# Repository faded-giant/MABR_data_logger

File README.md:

## Calibrating O2 Sensor

1. Replace ```port="COM8"``` with port number currently assigned to O2 Sensor in ```modbus.py```.
2. Run ``` pip3 install pymodbus```, if necessary in terminal.
3. Run ```python3 modbus.py``` in the directory ```modbus.py``` is located.
4. Script should display ```Raw value: <RAW DEVICE CURRENT> mA, Mapped value: <O2 BASED ON CAL POINTS>%"```
5. Perform a 3 point calibration as follows:
   - For 0% oxygen (```percent_1```), apply pure nitrogen gas to O2 sensor, note raw device current after it is stable.
   - For 10.475% oxygen (```percent_2```), apply a 50% nitrogren gas, 50% Air mixture to O2 sensor, note raw device current after it is stable.
   - For 20.95% oxygen (```percent_3```), apply 100% air to to O2 sensor, note raw device current after it is stable.

6. Replace ```current_1,current_2,current_3``` repectfully with the values noted in previous step.
7. Verify ```Mapped Value``` is as expected for the 3 calibration gases.
8. If all is expected, inside ```config.json```, update the ```current_1,current_2,current_3``` fields in the ```O2_sensor_calibration``` object.

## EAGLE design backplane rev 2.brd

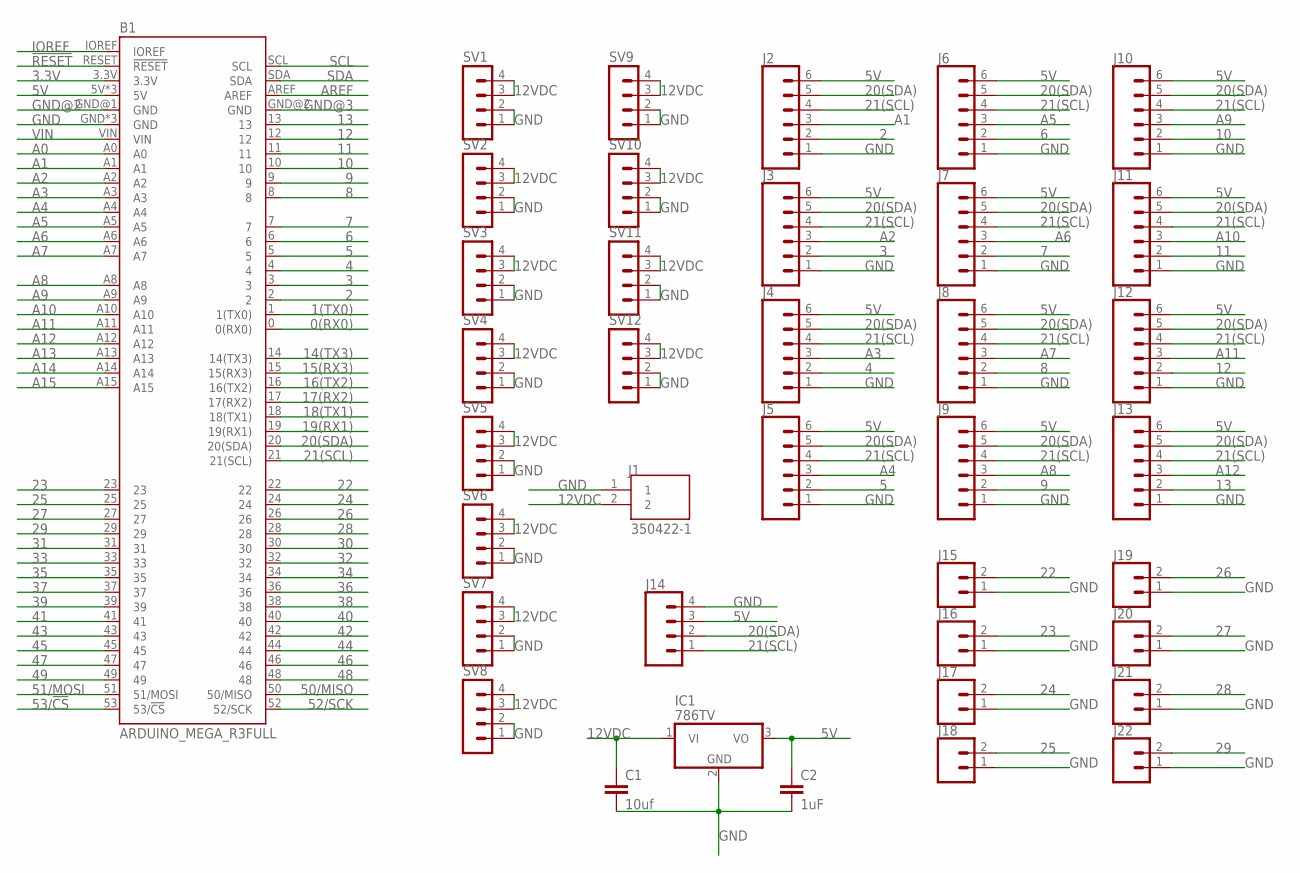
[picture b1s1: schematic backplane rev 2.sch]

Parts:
B1: ARDUINO_MEGA_R3FULL; ARDUINO_MEGA_NO_SILK
C1: 10uf; C2.5-3
C2: 1uF; C2.5-3
IC1: 786TV; TO220V
J1: 350422-1; POWER-PIN
J2, J3, J4, J5, J6, J7, J8, J9, J10, J11, J12, J13: CONN_06NO_SILK_FEMALE_PTH; 1X06_NO_SILK
J14: CONN_04PTH; 1X04
J15, J16, J17, J18, J19, J20, J21, J22: CONN_02; 1X02
SV1, SV2, SV3, SV4, SV5, SV6, SV7, SV8, SV9, SV10, SV11, SV12: MA04-1

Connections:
0(RX0): B1.0 (0(RX0))
1(TX0): B1.1 (1(TX0))
2: B1.2, J2.2
3: B1.3, J3.2
3.3V: B1.3.3V
4: B1.4, J4.2
5: B1.5, J5.2
5V: B1.5V, B1.5V@1 (5V), B1.5V@2 (5V), C2.1, IC1.3 (VO), J2.6, J3.6, J4.6, J5.6, J6.6, J7.6, J8.6, J9.6, J10.6, J11.6, J12.6, J13.6, J14.3
6: B1.6, J6.2
7: B1.7, J7.2
8: B1.8, J8.2
9: B1.9, J9.2
10: B1.10, J10.2
11: B1.11, J11.2
12: B1.12, J12.2
12VDC: C1.1, IC1.1 (VI), J1.2, SV1.3, SV1.4, SV2.3, SV2.4, SV3.3, SV3.4, SV4.3, SV4.4, SV5.3, SV5.4, SV6.3, SV6.4, SV7.3, SV7.4, SV8.3, SV8.4, SV9.3, SV9.4, SV10.3, SV10.4, SV11.3, SV11.4, SV12.3, SV12.4
13: B1.13, J13.2
14(TX3): B1.14 (14(TX3))
15(RX3): B1.15 (15(RX3))
16(TX2): B1.16 (16(TX2))
17(RX2): B1.17 (17(RX2))
18(TX1): B1.18 (18(TX1))
19(RX1): B1.19 (19(RX1))
20(SDA): B1.20 (20(SDA)), J2.5, J3.5, J4.5, J5.5, J6.5, J7.5, J8.5, J9.5, J10.5, J11.5, J12.5, J13.5, J14.2
21(SCL): B1.21 (21(SCL)), J2.4, J3.4, J4.4, J5.4, J6.4, J7.4, J8.4, J9.4, J10.4, J11.4, J12.4, J13.4, J14.1
22: B1.22, J15.2
23: B1.23, J16.2
24: B1.24, J17.2
25: B1.25, J18.2
26: B1.26, J19.2
27: B1.27, J20.2
28: B1.28, J21.2
29: B1.29, J22.2
30: B1.30
31: B1.31
32: B1.32
33: B1.33
34: B1.34
35: B1.35
36: B1.36
37: B1.37
38: B1.38
39: B1.39
40: B1.40
41: B1.41
42: B1.42
43: B1.43
44: B1.44
45: B1.45
46: B1.46
47: B1.47
48: B1.48
49: B1.49
50/MISO: B1.50 (50/MISO)
51/MOSI: B1.51 (51/MOSI)
52/SCK: B1.52 (52/SCK)
53/!CS: B1.53 (53/!CS)
!RESET: B1.RESET (!RESET)
A0: B1.A0
A1: B1.A1, J2.3
A2: B1.A2, J3.3
A3: B1.A3, J4.3
A4: B1.A4, J5.3
A5: B1.A5, J6.3
A6: B1.A6, J7.3
A7: B1.A7, J8.3
A8: B1.A8, J9.3
A9: B1.A9, J10.3
A10: B1.A10, J11.3
A11: B1.A11, J12.3
A12: B1.A12, J13.3
A13: B1.A13
A14: B1.A14
A15: B1.A15
AREF: B1.AREF
GND: B1.GND, B1.GND@3 (GND), B1.GND@4 (GND), C1.2, C2.2, IC1.2 (GND), J1.1, J2.1, J3.1, J4.1, J5.1, J6.1, J7.1, J8.1, J9.1, J10.1, J11.1, J12.1, J13.1, J14.4, J15.1, J16.1, J17.1, J18.1, J19.1, J20.1, J21.1, J22.1, SV1.1, SV1.2, SV2.1, SV2.2, SV3.1, SV3.2, SV4.1, SV4.2, SV5.1, SV5.2, SV6.1, SV6.2, SV7.1, SV7.2, SV8.1, SV8.2, SV9.1, SV9.2, SV10.1, SV10.2, SV11.1, SV11.2, SV12.1, SV12.2
GND@2: B1.GND@1 (GND)
GND@3: B1.GND@2 (GND)
IOREF: B1.IOREF
SCL: B1.SCL
SDA: B1.SDA
VIN: B1.VIN

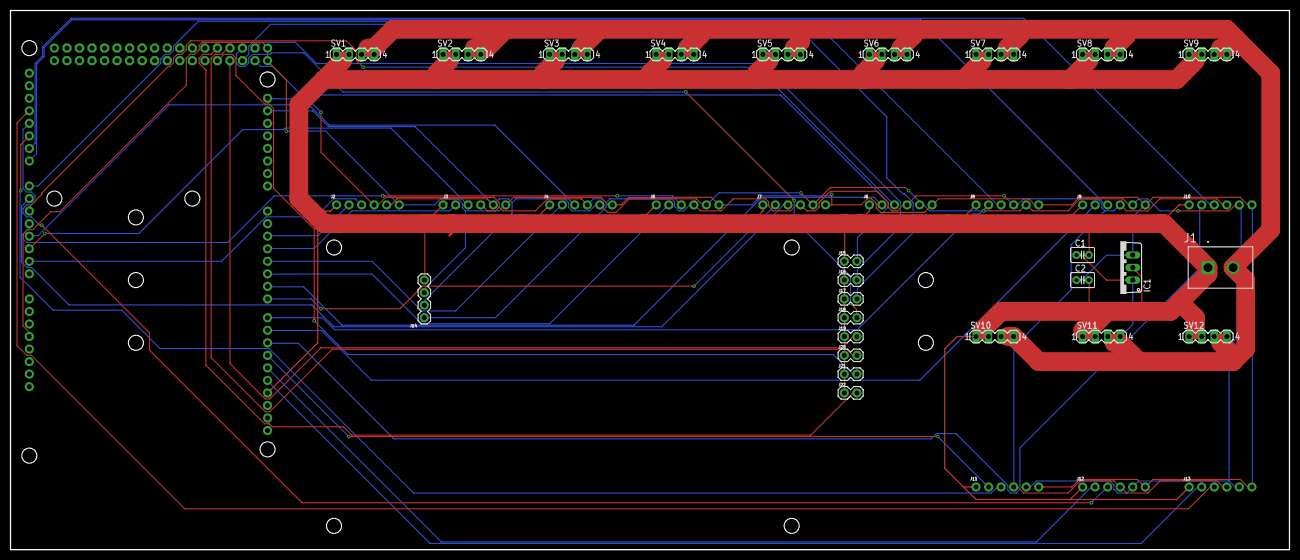
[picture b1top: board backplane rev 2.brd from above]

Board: 2 copper layers, 259.1 x 109.2 mm, 38 parts (1 on the bottom side), 37 nets.

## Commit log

2023-05-09 test commit
2023-05-09 clean wipe
2023-05-09 test
2023-05-09 run without stuff
2023-05-09 implemented ignoring device flags
2023-05-09 added toggle buttons
2023-05-09 fixed race conditon for opening window
2023-05-10 testing new update script
2023-05-10 fixed close button bug
2023-05-10 put for loops in try blocks
2023-05-10 print traceback
2023-05-10 pass execption
2023-05-10 added sonde
2023-05-10 cleaned up dir
2023-05-11 changed a thing
2023-05-11 deleted that thing
2023-05-16 scaled down displayed sizes
2023-06-14 schematic for backplane added to repo
2024-06-04 added modbus.py, used to read raw current values
2025-02-25 Add files via upload
    added current version of logger.py, and fields for flow sensor

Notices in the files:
parts and their libraries:
SparkFun-Boards: Licensing: Creative Commons ShareAlike 4.0 International - https://creativecommons.org/licenses/by-sa/4.0
